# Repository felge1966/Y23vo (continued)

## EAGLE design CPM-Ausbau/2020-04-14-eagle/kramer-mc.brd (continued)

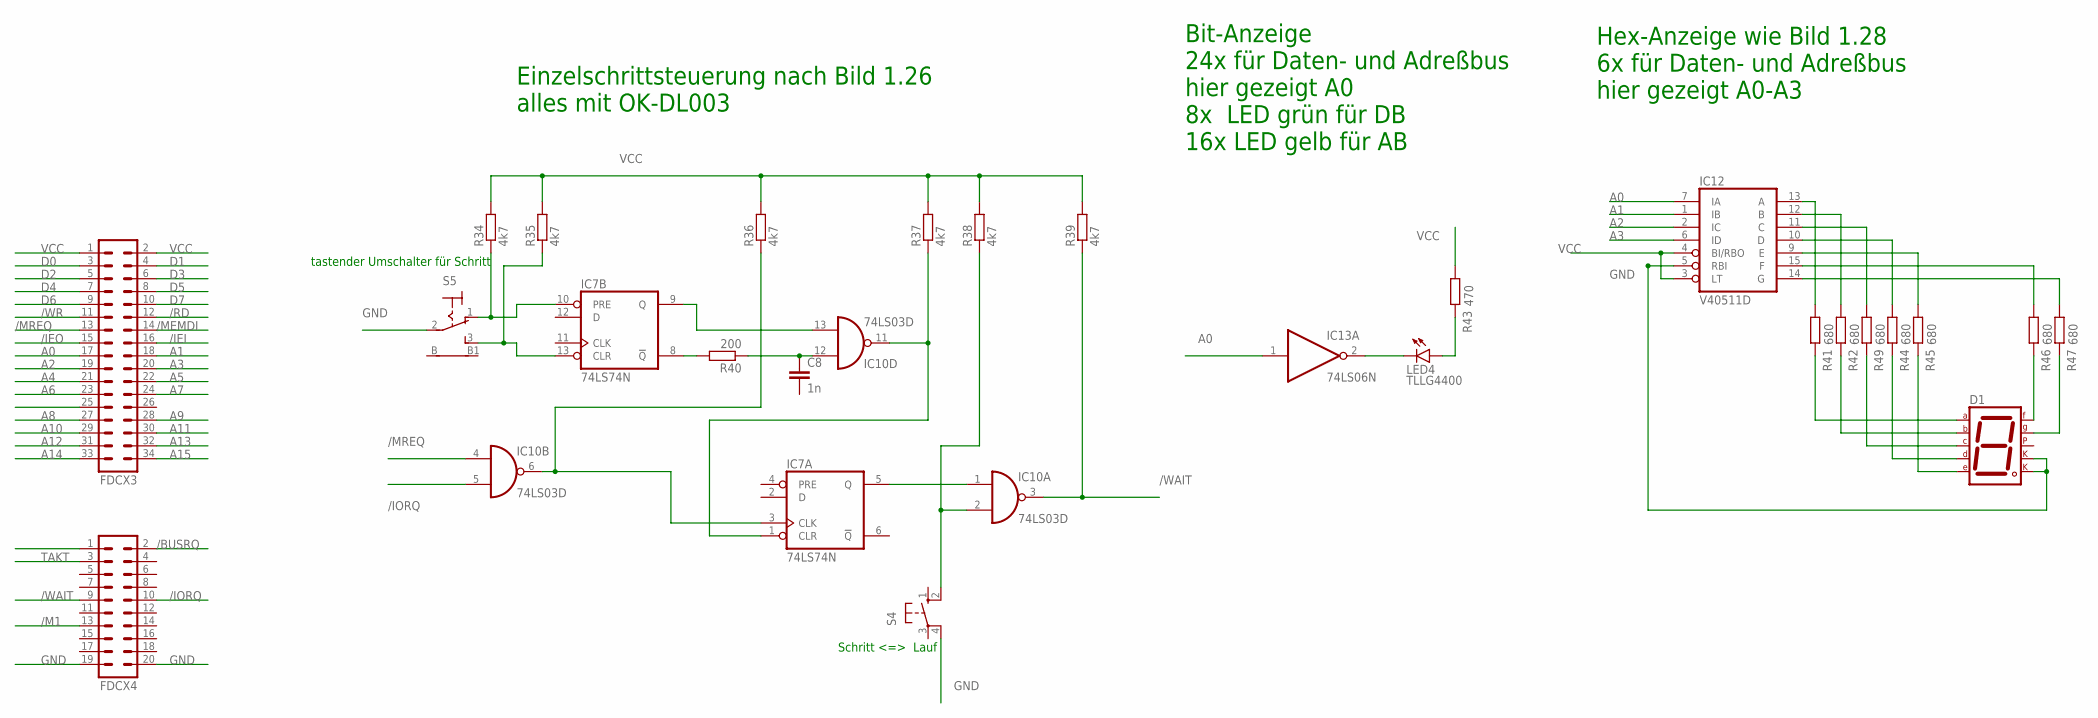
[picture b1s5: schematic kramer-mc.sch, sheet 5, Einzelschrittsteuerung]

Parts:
C8: 1n; C050-024X044
D1: 7SEG-CK; 7SEG-13
FDCX3: ML34
FDCX4: ML20
IC7: 74LS74N; DIL14
IC10: 74LS03D; SO14
IC12: V40511D; DIL16
IC13: 74LS06N; DIL14
LED4: TLLG4400; LED3MM
R34, R35, R36, R37, R38, R39: 4k7; 0309/12
R40: 200; 0309/12
R41, R42, R44, R45, R46, R47, R49: 680; 0309/12
R43: 470; 0309/12
S4: 10-XX; B3F-10XX
S5: 316-917

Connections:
/BUSRQ: FDCX4.2; also elsewhere on the board
/CSBWS1: FDCX3.25
/IEI: FDCX3.16; also elsewhere on the board
/IEO: FDCX3.15; also elsewhere on the board
/IORQ: FDCX4.10, IC10.5 (I1); also elsewhere on the board
/M1: FDCX4.13; also elsewhere on the board
/MEMDI: FDCX3.14; also elsewhere on the board
/MREQ: FDCX3.13, IC10.4 (I0); also elsewhere on the board
/RD: FDCX3.12; also elsewhere on the board
/RESET1: FDCX4.1
/WAIT: FDCX4.9, IC10.3 (O), R39.1; also elsewhere on the board
/WR: FDCX3.11; also elsewhere on the board
A0: FDCX3.17, IC12.7 (IA), IC13.1 (I); also elsewhere on the board
A1: FDCX3.18, IC12.1 (IB); also elsewhere on the board
A2: FDCX3.19, IC12.2 (IC); also elsewhere on the board
A3: FDCX3.20, IC12.6 (ID); also elsewhere on the board
A4: FDCX3.21; also elsewhere on the board
A5: FDCX3.22; also elsewhere on the board
A6: FDCX3.23; also elsewhere on the board
A7: FDCX3.24; also elsewhere on the board
A8: FDCX3.27; also elsewhere on the board
A9: FDCX3.28; also elsewhere on the board
A10: FDCX3.29; also elsewhere on the board
A11: FDCX3.30; also elsewhere on the board
A12: FDCX3.31; also elsewhere on the board
A13: FDCX3.32; also elsewhere on the board
A14: FDCX3.33; also elsewhere on the board
A15: FDCX3.34; also elsewhere on the board
D0: FDCX3.3; also elsewhere on the board
D1: FDCX3.4; also elsewhere on the board
D2: FDCX3.5; also elsewhere on the board
D3: FDCX3.6; also elsewhere on the board
D4: FDCX3.7; also elsewhere on the board
D5: FDCX3.8; also elsewhere on the board
D6: FDCX3.9; also elsewhere on the board
D7: FDCX3.10; also elsewhere on the board
GND: D1.3 (CK1), D1.8 (CK2), FDCX4.19, FDCX4.20, IC7.7 (GND), IC10.7 (GND), IC12.5 (RBI), IC12.8 (GND), IC13.7 (GND), S4.4 (P1), S5.2; also elsewhere on the board
unnamed: IC7.10 (PRE), R34.1, S5.1 (O)
unnamed: IC7.13 (CLR), R35.1, S5.3 (S)
unnamed: IC7.9 (Q), IC10.13 (I1)
unnamed: IC12.13 (A), R41.1
unnamed: IC7.8 (!Q), R40.2
unnamed: C8.1, IC10.12 (I0), R40.1
unnamed: IC7.1 (CLR), IC10.11 (O), R37.1
unnamed: IC10.2 (I1), R38.1, S4.2 (S1)
unnamed: IC7.5 (Q), IC10.1 (I0)
unnamed: IC12.12 (B), R42.1
unnamed: IC7.3 (CLK), IC10.6 (O), R36.1
unnamed: IC12.11 (C), R49.1
unnamed: IC12.10 (D), R44.1
unnamed: IC12.9 (E), R45.1
unnamed: IC13.2 (O), LED4.K (C)
unnamed: LED4.A, R43.2
unnamed: IC12.15 (F), R46.1
unnamed: IC12.14 (G), R47.1
unnamed: D1.7 (A), R41.2
unnamed: D1.6 (B), R42.2
unnamed: D1.10 (G), R47.2
unnamed: D1.9 (F), R46.2
unnamed: D1.4 (C), R49.2
unnamed: D1.2 (D), R44.2
unnamed: D1.1 (E), R45.2
TAKT: FDCX4.3; also elsewhere on the board
VCC: FDCX3.1, FDCX3.2, IC7.14 (VCC), IC10.14 (VCC), IC12.3 (LT), IC12.4 (BI/RBO), IC12.16 (VCC), IC13.14 (VCC), R34.2, R35.2, R36.2, R37.2, R38.2, R39.2, R43.1; also elsewhere on the board

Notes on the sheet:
tastender Umschalter für Schritt
Schritt <=> Lauf
Einzelschrittsteuerung nach Bild 1.26 alles mit OK-DL003
Hex-Anzeige wie Bild 1.28 6x für Daten- und Adreßbus hier gezeigt A0-A3
Bit-Anzeige 24x für Daten- und Adreßbus hier gezeigt A0 8x LED grün für DB 16x LED gelb für AB

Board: 2 copper layers, 159 parts (0 on the bottom side), 286 nets, no tracks yet.

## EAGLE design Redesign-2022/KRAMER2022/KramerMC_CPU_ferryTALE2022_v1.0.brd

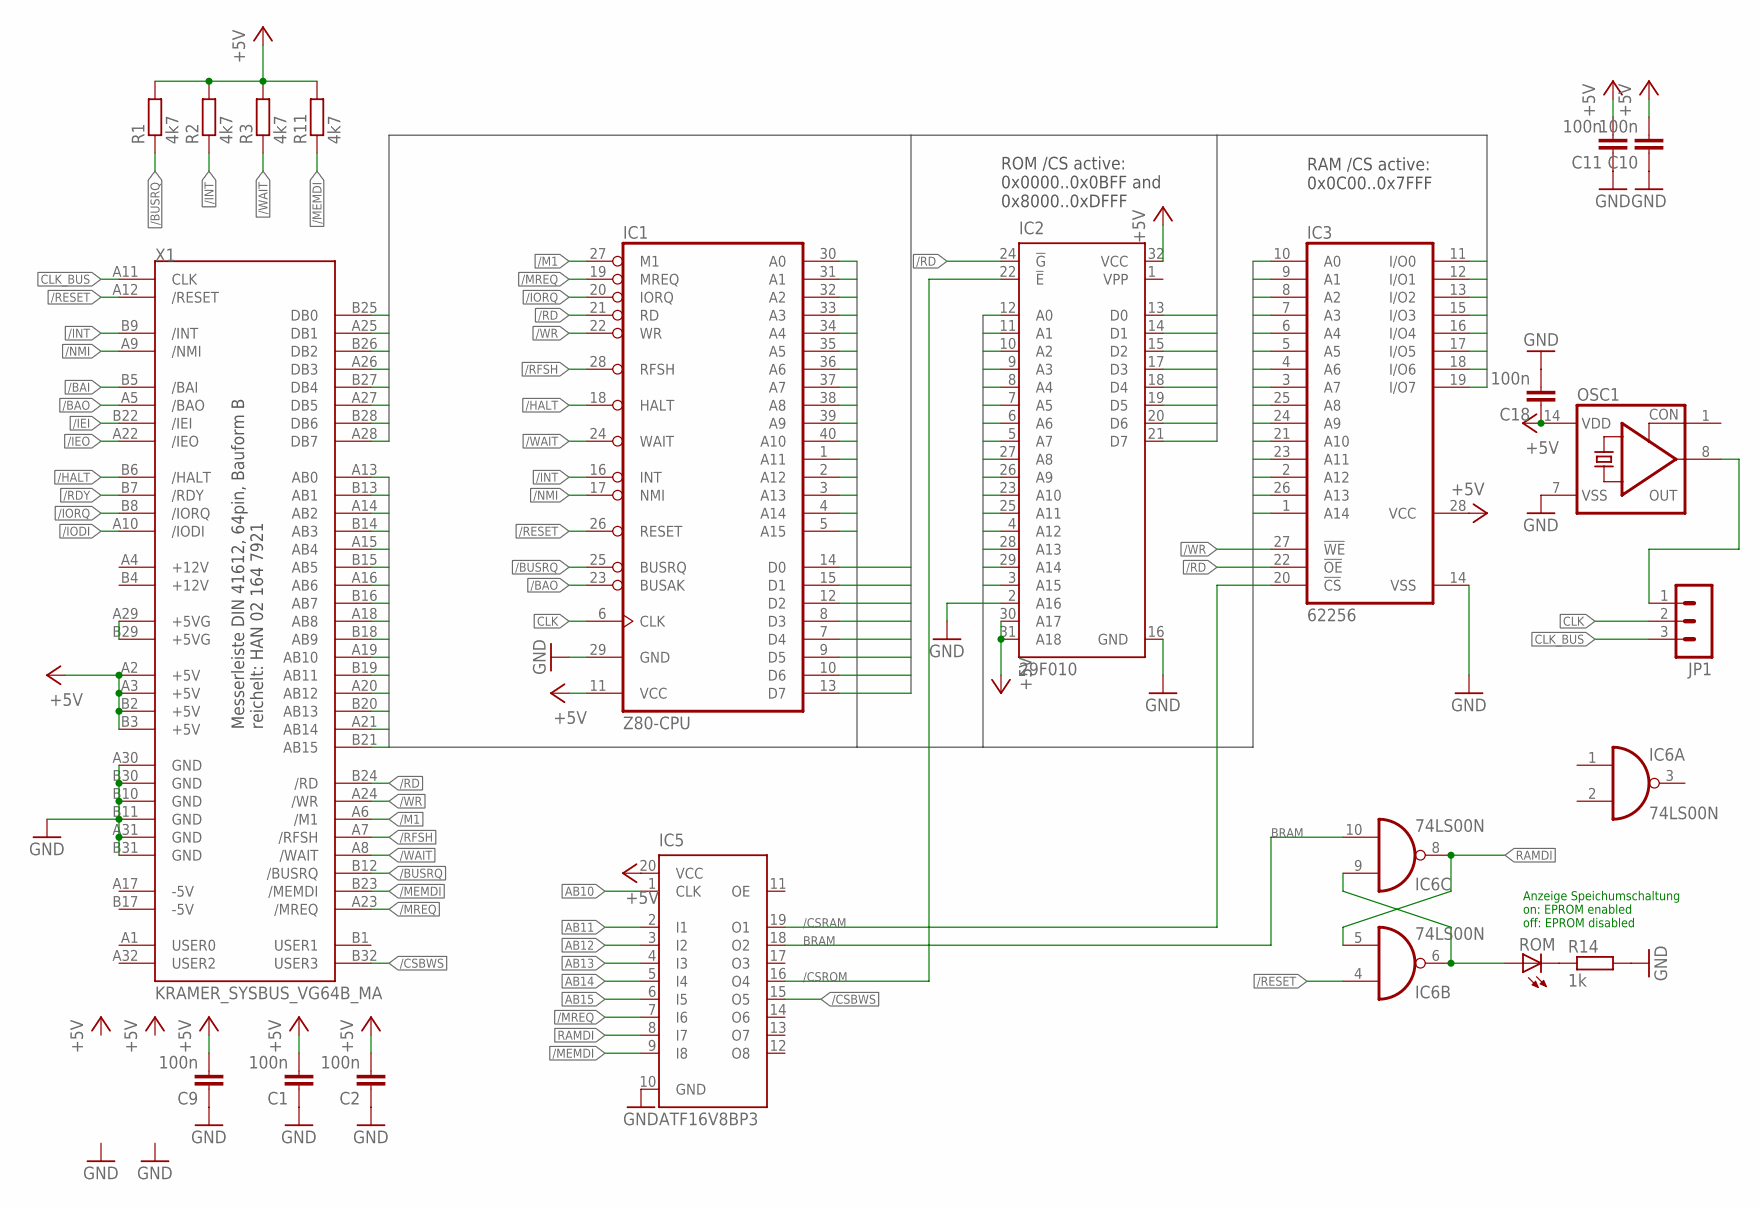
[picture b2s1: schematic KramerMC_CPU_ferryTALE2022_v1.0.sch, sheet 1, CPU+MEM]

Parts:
C1, C2, C9, C10, C11, C18: 100n; C050-024X044
IC1: Z80-CPU; DIL40
IC2: 29F010; DIL32
IC3: 62256; DIL28-6
IC5: ATF16V8BP3; DIL20
IC6: 74LS00N; DIL14
JP1: MA03-1
OSC1: CRYSTAL_RES-SG51; SG51
R1, R2, R3, R11: 4k7; 0207/10
R14: 1k; 0207/10
ROM: LED3MM
X1: KRAMER_SYSBUS_VG64B_MA; MAB64

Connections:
+5V: C1.2, C2.2, C9.2, C10.2, C11.2, C18.1, IC1.11 (VCC), IC2.30 (A17), IC2.31 (A18), IC2.32 (VCC), IC3.28 (VCC), IC5.20 (VCC), OSC1.14 (VDD), R1.2, R2.2, R3.2, R11.2, X1.A2 (+5V), X1.A3 (+5V), X1.B2 (+5V), X1.B3 (+5V); also elsewhere on the board
+5VG: X1.A29 (+5VG), X1.B29 (+5VG)
/BAI: X1.B5 (/BAI)
/BAO: IC1.23 (BUSAK), X1.A5 (/BAO)
/BUSRQ: IC1.25 (BUSRQ), R1.1, X1.B12 (/BUSRQ)
/CSBWS: IC5.15 (O5), X1.B32 (USER3)
/CSRAM: IC3.20 (!CS), IC5.19 (O1)
/CSROM: IC2.22 (!E), IC5.16 (O4)
/HALT: IC1.18 (HALT), X1.B6 (/HALT)
/IEI: X1.B22 (/IEI)
/IEO: X1.A22 (/IEO)
/INT: IC1.16 (INT), R2.1, X1.B9 (/INT); also elsewhere on the board
/IODI: X1.A10 (/IODI)
/IORQ: IC1.20 (IORQ), X1.B8 (/IORQ); also elsewhere on the board
/M1: IC1.27 (M1), X1.A6 (/M1); also elsewhere on the board
/MEMDI: IC5.9 (I8), R11.1, X1.B23 (/MEMDI)
/MREQ: IC1.19 (MREQ), IC5.7 (I6), X1.A23 (/MREQ)
/NMI: IC1.17 (NMI), X1.A9 (/NMI); also elsewhere on the board
/RD: IC1.21 (RD), IC2.24 (!G), IC3.22 (!OE), X1.B24 (/RD); also elsewhere on the board
/RDY: X1.B7 (/RDY)
/RESET: IC1.26 (RESET), IC6.4 (I0), X1.A12 (/RESET); also elsewhere on the board
/RFSH: IC1.28 (RFSH), X1.A7 (/RFSH)
/WAIT: IC1.24 (WAIT), R3.1, X1.A8 (/WAIT)
/WR: IC1.22 (WR), IC3.27 (!WE), X1.A24 (/WR)
AB0: IC1.30 (A0), IC2.12 (A0), IC3.10 (A0), X1.A13 (AB0); also elsewhere on the board
AB1: IC1.31 (A1), IC2.11 (A1), IC3.9 (A1), X1.B13 (AB1); also elsewhere on the board
AB2: IC1.32 (A2), IC2.10 (A2), IC3.8 (A2), X1.A14 (AB2)
AB3: IC1.33 (A3), IC2.9 (A3), IC3.7 (A3), X1.B14 (AB3)
AB4: IC1.34 (A4), IC2.8 (A4), IC3.6 (A4), X1.A15 (AB4)
AB5: IC1.35 (A5), IC2.7 (A5), IC3.5 (A5), X1.B15 (AB5)
AB6: IC1.36 (A6), IC2.6 (A6), IC3.4 (A6), X1.A16 (AB6); also elsewhere on the board
AB7: IC1.37 (A7), IC2.5 (A7), IC3.3 (A7), X1.B16 (AB7); also elsewhere on the board
AB8: IC1.38 (A8), IC2.27 (A8), IC3.25 (A8), X1.A18 (AB8)
AB9: IC1.39 (A9), IC2.26 (A9), IC3.24 (A9), X1.B18 (AB9)
AB10: IC1.40 (A10), IC2.23 (A10), IC3.21 (A10), IC5.1 (CLK), X1.A19 (AB10)
AB11: IC1.1 (A11), IC2.25 (A11), IC3.23 (A11), IC5.2 (I1), X1.B19 (AB11)
AB12: IC1.2 (A12), IC2.4 (A12), IC3.2 (A12), IC5.3 (I2), X1.A20 (AB12)
AB13: IC1.3 (A13), IC2.28 (A13), IC3.26 (A13), IC5.4 (I3), X1.B20 (AB13)
AB14: IC1.4 (A14), IC2.29 (A14), IC3.1 (A14), IC5.5 (I4), X1.A21 (AB14)
AB15: IC1.5 (A15), IC2.3 (A15), IC5.6 (I5), X1.B21 (AB15)
BRAM: IC5.18 (O2), IC6.10 (I1)
CLK: IC1.6 (CLK), JP1.2; also elsewhere on the board
CLK_BUS: JP1.3, X1.A11 (CLK)
DB0: IC1.14 (D0), IC2.13 (D0), IC3.11 (I/O0), X1.B25 (DB0); also elsewhere on the board
DB1: IC1.15 (D1), IC2.14 (D1), IC3.12 (I/O1), X1.A25 (DB1); also elsewhere on the board
DB2: IC1.12 (D2), IC2.15 (D2), IC3.13 (I/O2), X1.B26 (DB2); also elsewhere on the board
DB3: IC1.8 (D3), IC2.17 (D3), IC3.15 (I/O3), X1.A26 (DB3); also elsewhere on the board
DB4: IC1.7 (D4), IC2.18 (D4), IC3.16 (I/O4), X1.B27 (DB4); also elsewhere on the board
DB5: IC1.9 (D5), IC2.19 (D5), IC3.17 (I/O5), X1.A27 (DB5); also elsewhere on the board
DB6: IC1.10 (D6), IC2.20 (D6), IC3.18 (I/O6), X1.B28 (DB6); also elsewhere on the board
DB7: IC1.13 (D7), IC2.21 (D7), IC3.19 (I/O7), X1.A28 (DB7); also elsewhere on the board
GND: C1.1, C2.1, C9.1, C10.1, C11.1, C18.2, IC1.29 (GND), IC2.2 (A16), IC2.16 (GND), IC3.14 (VSS), IC5.10 (GND), OSC1.7 (VSS), R14.2, X1.A30 (GND), X1.A31 (GND), X1.B10 (GND), X1.B11 (GND), X1.B30 (GND), X1.B31 (GND); also elsewhere on the board
unnamed: IC6.6 (O), IC6.9 (I0), ROM.A
unnamed: R14.1, ROM.K (C)
unnamed: JP1.1, OSC1.8 (OUT)
RAMDI: IC5.8 (I7), IC6.5 (I1), IC6.8 (O)
VPP: IC2.1 (VPP)

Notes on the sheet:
RAM /CS active: 0x0C00..0x7FFF
ROM /CS active: 0x0000..0x0BFF and 0x8000..0xDFFF
Anzeige Speichumschaltung on: EPROM enabled off: EPROM disabled
Messerleiste DIN 41612, 64pin, Bauform B reichelt: HAN 02 164 7921

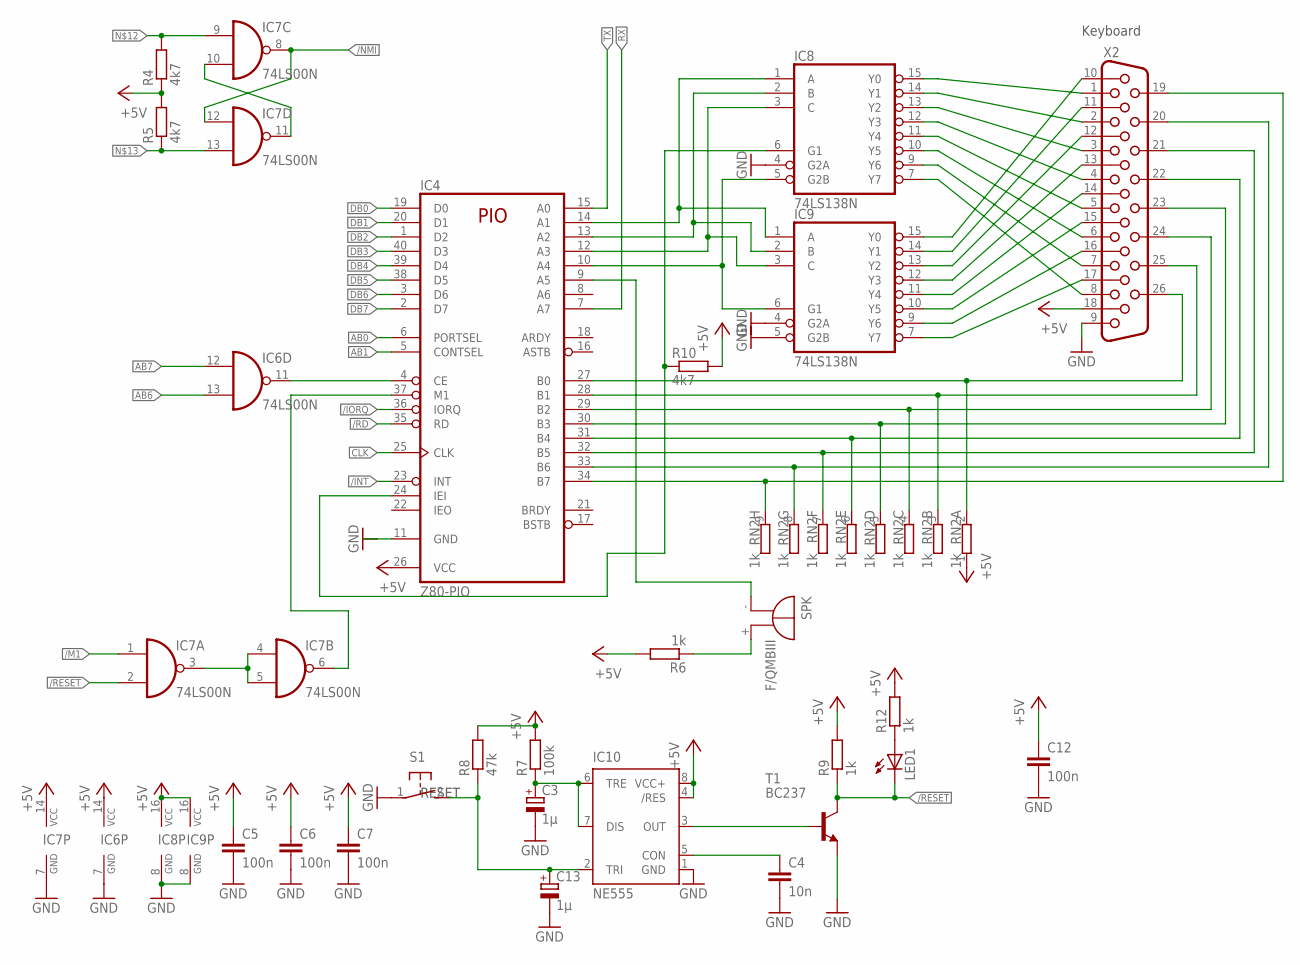
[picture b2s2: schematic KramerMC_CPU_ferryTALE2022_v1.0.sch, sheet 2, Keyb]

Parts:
C3, C13: 1µ; E2-5
C4: 10n; C050-024X044
C5, C6, C7, C12: 100n; C050-024X044
IC4: Z80-PIO; DIL40
IC6, IC7: 74LS00N; DIL14
IC8, IC9: 74LS138N; DIL16
IC10: NE555; DIL-08
LED1: LED3MM
R4, R5, R10: 4k7; 0207/10
R6: 1k; 0207/10
R7: 100k; 0207/2V
R8: 47k; 0207/10
R9, R12: 1k; 0207/2V
RN2: 1k; SIL9
S1: 31-XX; B3F-31XX
SPK: F/QMBIII
T1: BC237; TO92
X2: HF26H; HDF26H

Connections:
+5V: C5.1, C6.1, C7.1, C12.1, IC4.26 (VCC), IC6.14 (VCC), IC7.14 (VCC), IC8.16 (VCC), IC9.16 (VCC), IC10.4 (/RES), IC10.8 (VCC+), R4.1, R5.2, R6.2, R7.2, R8.2, R9.2, R10.2, R12.2, RN2.1, X2.18; also elsewhere on the board
/INT: IC4.23 (INT); also elsewhere on the board
/IORQ: IC4.36 (IORQ); also elsewhere on the board
/M1: IC7.1 (I0); also elsewhere on the board
/NMI: IC7.8 (O), IC7.12 (I0); also elsewhere on the board
/RD: IC4.35 (RD); also elsewhere on the board
/RESET: IC7.2 (I1), LED1.K (C), R9.1, T1.3 (C); also elsewhere on the board
AB0: IC4.6 (PORTSEL); also elsewhere on the board
AB1: IC4.5 (CONTSEL); also elsewhere on the board
AB6: IC6.13 (I1); also elsewhere on the board
AB7: IC6.12 (I0); also elsewhere on the board
CLK: IC4.25 (CLK); also elsewhere on the board
DB0: IC4.19 (D0); also elsewhere on the board
DB1: IC4.20 (D1); also elsewhere on the board
DB2: IC4.1 (D2); also elsewhere on the board
DB3: IC4.40 (D3); also elsewhere on the board
DB4: IC4.39 (D4); also elsewhere on the board
DB5: IC4.38 (D5); also elsewhere on the board
DB6: IC4.3 (D6); also elsewhere on the board
DB7: IC4.2 (D7); also elsewhere on the board
GND: C3.-, C4.2, C5.2, C6.2, C7.2, C12.2, C13.-, IC4.11 (GND), IC6.7 (GND), IC7.7 (GND), IC8.4 (G2A), IC8.8 (GND), IC9.4 (G2A), IC9.5 (G2B), IC9.8 (GND), IC10.1 (GND), S1.1, T1.1 (E), X2.9; also elsewhere on the board
unnamed: LED1.A, R12.1
unnamed: IC8.15 (Y0), X2.1
unnamed: IC7.10 (I1), IC7.11 (O)
unnamed: IC7.9 (I0), R4.2
unnamed: IC7.13 (I1), R5.1
unnamed: IC4.14 (A1), IC8.1 (A), IC9.1 (A)
unnamed: IC4.13 (A2), IC8.2 (B), IC9.2 (B)
unnamed: IC4.12 (A3), IC8.3 (C), IC9.3 (C)
unnamed: IC7.3 (O), IC7.4 (I0), IC7.5 (I1)
unnamed: IC8.14 (Y1), X2.2
unnamed: IC4.4 (CE), IC6.11 (O)
unnamed: IC4.37 (M1), IC7.6 (O)
unnamed: IC8.13 (Y2), X2.3
unnamed: IC8.12 (Y3), X2.4
unnamed: IC8.11 (Y4), X2.5
unnamed: IC8.10 (Y5), X2.6
unnamed: IC8.9 (Y6), X2.7
unnamed: IC8.7 (Y7), X2.8
unnamed: IC4.27 (B0), RN2.2, X2.26
unnamed: IC4.28 (B1), RN2.3 (2), X2.25
unnamed: IC4.29 (B2), RN2.4 (2), X2.24
unnamed: IC4.30 (B3), RN2.5 (2), X2.23
unnamed: IC4.31 (B4), RN2.6 (2), X2.22
unnamed: IC4.32 (B5), RN2.7 (2), X2.21
unnamed: IC4.33 (B6), RN2.8 (2), X2.20
unnamed: IC4.34 (B7), RN2.9 (2), X2.19
unnamed: IC4.9 (A5), SPK.- (+)
unnamed: IC10.3 (OUT), T1.2 (B)
unnamed: C3.+, IC10.6 (TRE), IC10.7 (DIS), R7.1
unnamed: C4.1, IC10.5 (CON)
unnamed: R6.1, SPK.+ (-)
unnamed: IC4.24 (IEI), IC8.6 (G1), R10.1
unnamed: IC4.10 (A4), IC8.5 (G2B), IC9.6 (G1)
unnamed: IC9.15 (Y0), X2.10
unnamed: IC9.14 (Y1), X2.11
unnamed: IC9.13 (Y2), X2.12
unnamed: IC9.12 (Y3), X2.13
unnamed: IC9.11 (Y4), X2.14
unnamed: IC9.10 (Y5), X2.15
unnamed: IC9.9 (Y6), X2.16
unnamed: IC9.7 (Y7), X2.17
RESET_BUTTON: C13.+, IC10.2 (TRI), R8.1, S1.2 (S)
RX: IC4.7 (A7); also elsewhere on the board
TX: IC4.15 (A0); also elsewhere on the board

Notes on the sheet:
Keyboard
RESET

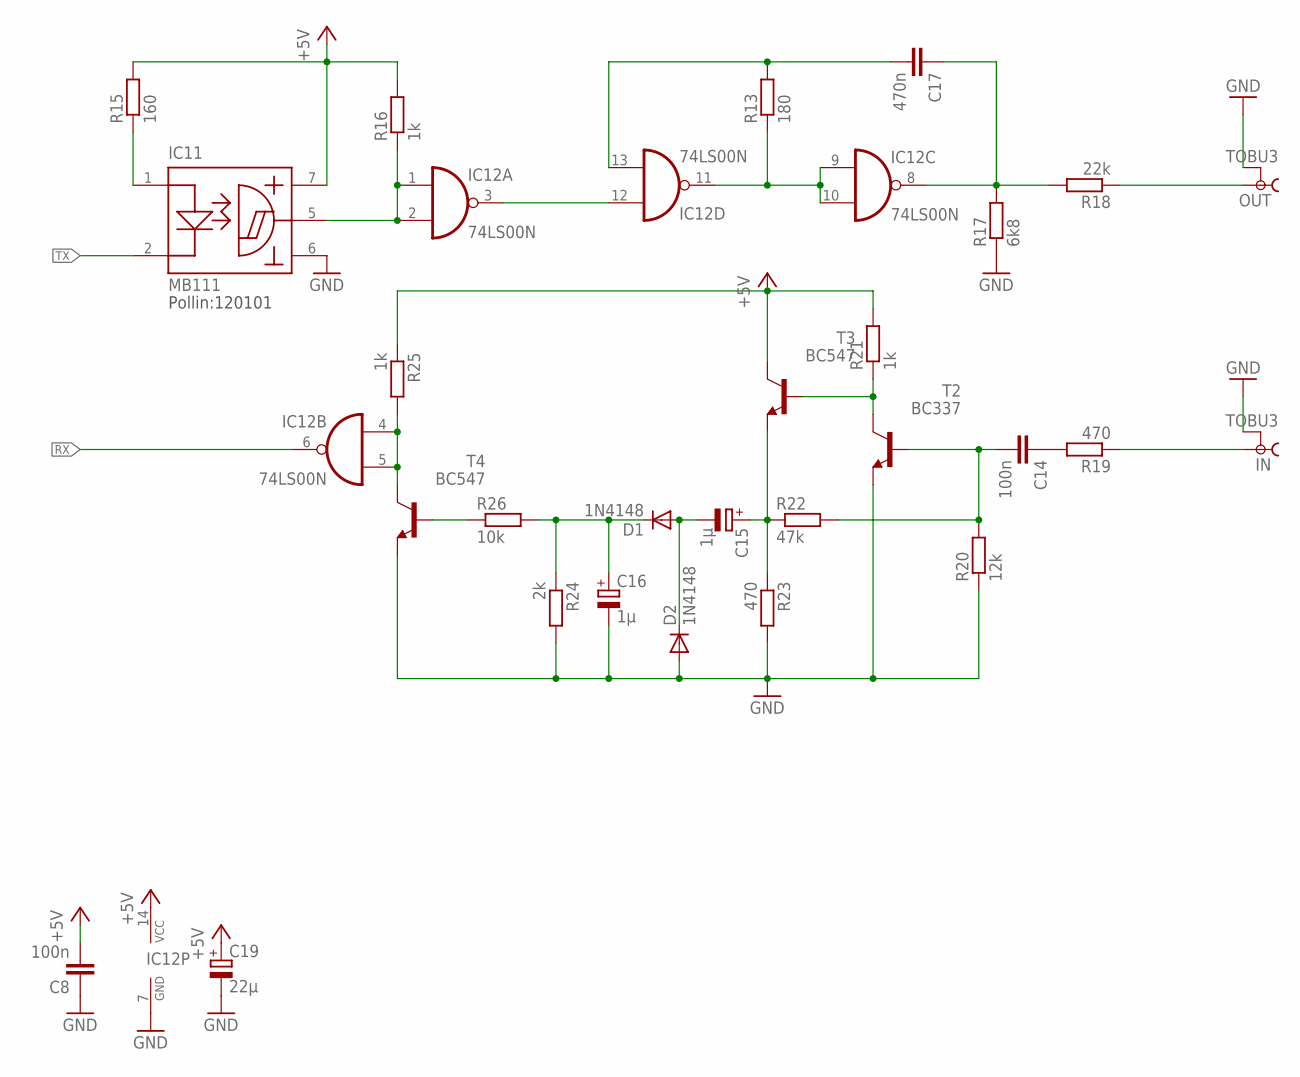
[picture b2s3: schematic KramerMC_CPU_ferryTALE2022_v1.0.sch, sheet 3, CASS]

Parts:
C8, C14: 100n; C050-024X044
C15, C16: 1µ; E2-4
C17: 470n; C050-024X044
C19: 22µ; E2-4
D1, D2: 1N4148; DO35-7
IC11: MB111; DIL08
IC12: 74LS00N; DIL14
IN: TOBU3
OUT: TOBU3
R13: 180; 0207/10
R15: 160; 0207/10
R16, R25: 1k; 0207/2V
R17: 6k8; 0207/10
R18: 22k; 0207/10
R19, R23: 470; 0207/10
R20: 12k; 0207/10
R21: 1k; 0207/10
R22: 47k; 0207/2V
R24: 2k; 0207/10
R26: 10k; 0207/10
T2: BC337; TO92
T3, T4: BC547; TO92

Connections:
+5V: C8.2, C19.+, IC11.7 (VCC), IC12.14 (VCC), R15.2, R16.2, R21.2, R25.1, T3.3 (C); also elsewhere on the board
GND: C8.1, C16.-, C19.-, D2.A, IC11.6 (GND), IC12.7 (GND), IN.2, IN.2@1 (2), IN.2@2 (2), OUT.2, OUT.2@1 (2), OUT.2@2 (2), R17.1, R20.1, R23.2, R24.2, T2.1 (E), T4.1 (E); also elsewhere on the board
unnamed: IC11.1 (A), R15.1
unnamed: IC12.3 (O), IC12.12 (I0)
unnamed: IC11.5 (OUT), IC12.1 (I0), IC12.2 (I1), R16.1
unnamed: C17.2, IC12.13 (I1), R13.2
unnamed: IC12.9 (I0), IC12.10 (I1), IC12.11 (O), R13.1
unnamed: OUT.1, R18.1
unnamed: IC12.4 (I0), IC12.5 (I1), R25.2, T4.3 (C)
unnamed: C14.1, R19.2
unnamed: C17.1, IC12.8 (O), R17.2, R18.2
unnamed: R21.1, T2.3 (C), T3.2 (B)
unnamed: C14.2, R20.2, R22.2, T2.2 (B)
unnamed: IN.1, R19.1
unnamed: R26.1, T4.2 (B)
unnamed: C16.+, D1.C, R24.1, R26.2
unnamed: C15.-, D1.A, D2.C
unnamed: C15.+, R22.1, R23.1, T3.1 (E)
RX: IC12.6 (O); also elsewhere on the board
TX: IC11.2 (K); also elsewhere on the board

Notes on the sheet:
Pollin:120101

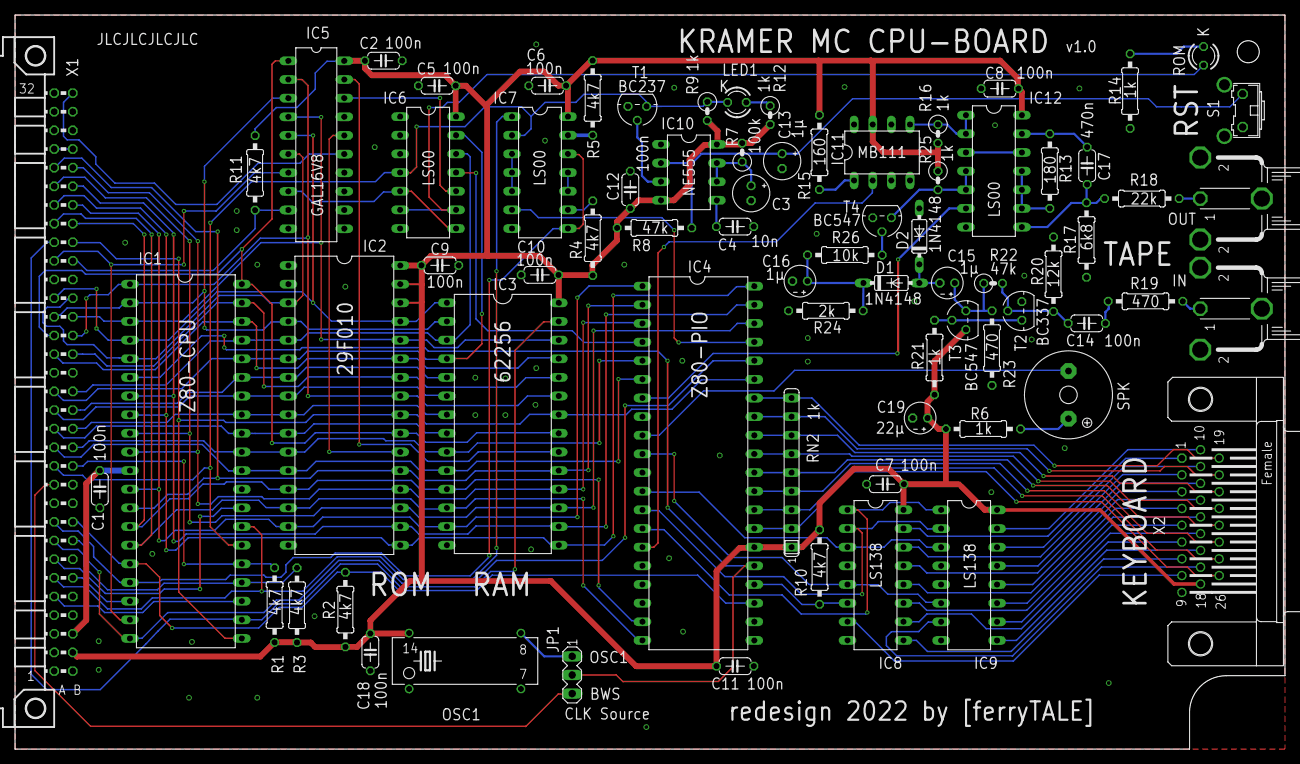
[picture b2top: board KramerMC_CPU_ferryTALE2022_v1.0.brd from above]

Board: 2 copper layers, 173.0 x 100.0 mm, 74 parts (0 on the bottom side), 111 nets.

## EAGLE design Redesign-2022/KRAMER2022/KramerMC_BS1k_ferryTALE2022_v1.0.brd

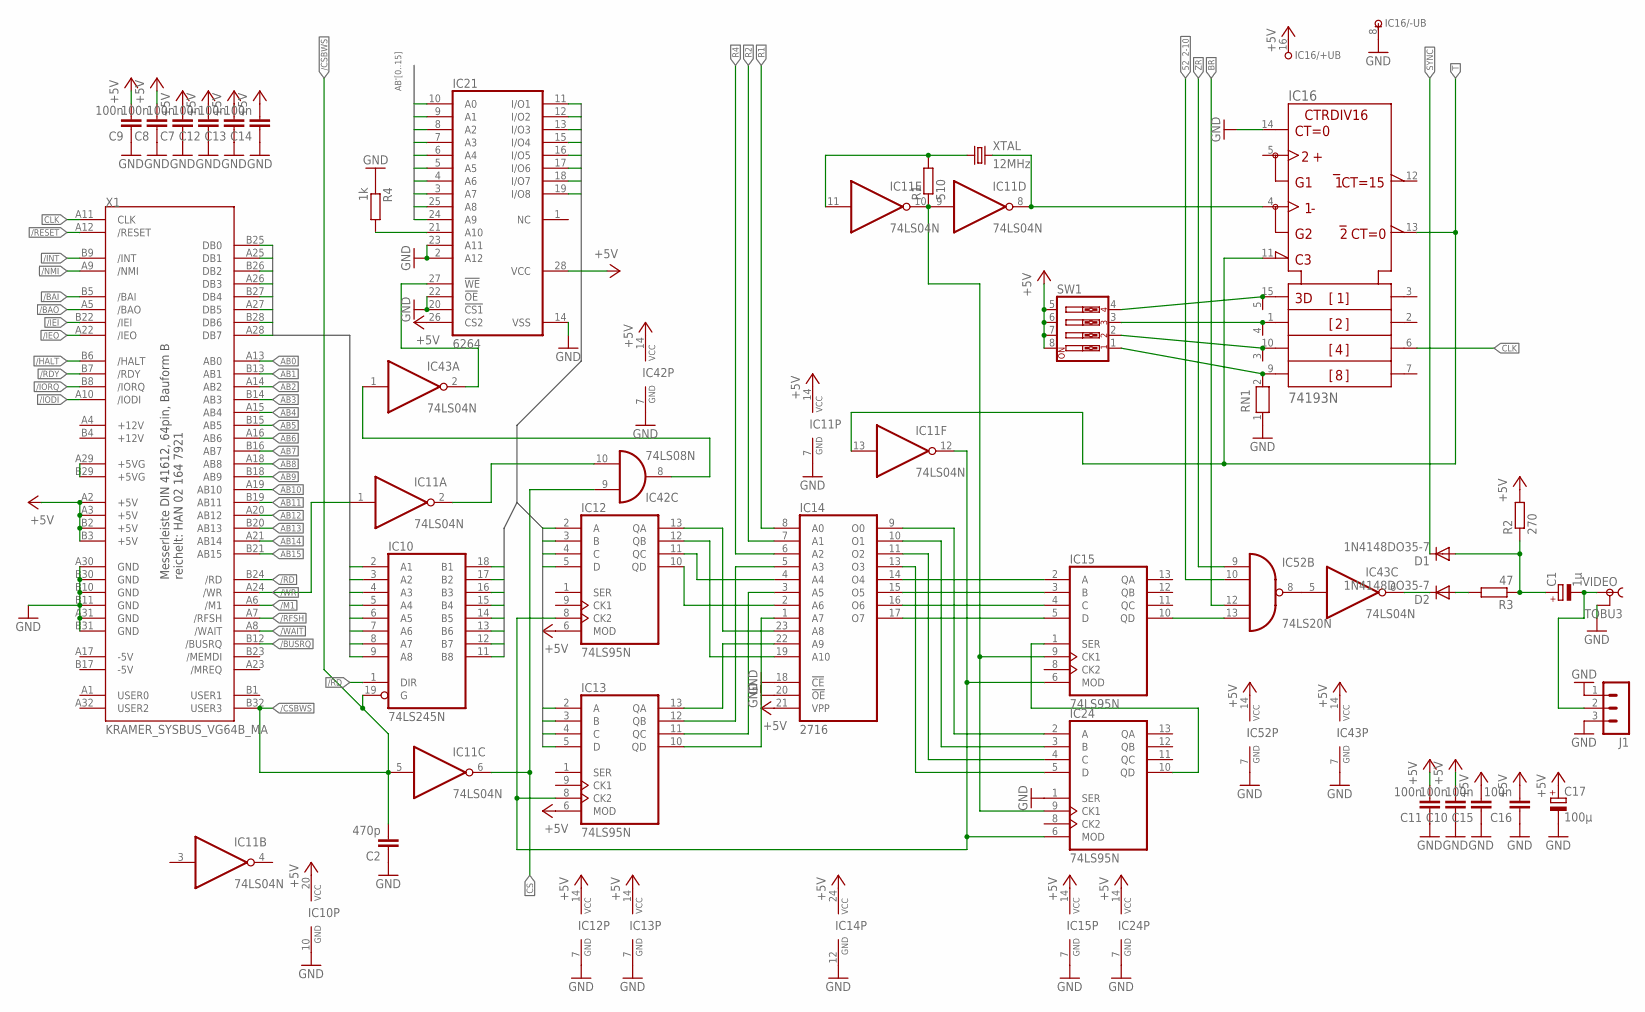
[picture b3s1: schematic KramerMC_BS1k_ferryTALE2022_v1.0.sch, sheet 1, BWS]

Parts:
C1: 1µ; E2,5-5
C2: 470p; C050-024X044
C7, C8, C9, C10, C11, C12, C13, C14, C15, C16: 100n; C050-024X044
C17: 100µ; E2,5-7
D1, D2: 1N4148DO35-7; DO35-7
IC10: 74LS245N; DIL20
IC11, IC43: 74LS04N; DIL14
IC12, IC13, IC15, IC24: 74LS95N; DIL14
IC14: 2716; DIL24
IC16: 74193N; DIL16
IC21: 6264; DIL28-6
IC42: 74LS08N; DIL14
IC52: 74LS20N; DIL14
J1: MA03-1
R1: 510; 0207/2V
R2: 270; 0207/10
R3: 47; 0207/10
R4: 1k; 0207/10
RN1: RN04; RN-5
SW1: SW_DIP-4; EDG-04
VIDEO: TOBU3
X1: KRAMER_SYSBUS_VG64B_MA; MAB64
XTAL: 12MHz; HC49/S

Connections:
52_2-10: IC52.10 (I1); also elsewhere on the board
+5V: C7.2, C8.2, C9.2, C10.2, C11.2, C12.2, C13.2, C14.2, C15.2, C16.2, C17.+, IC10.20 (VCC), IC11.14 (VCC), IC12.6 (MOD), IC12.14 (VCC), IC13.6 (MOD), IC13.14 (VCC), IC14.21 (VPP), IC14.24 (VCC), IC15.14 (VCC), IC16.16 (+UB), IC21.26 (CS2), IC21.28 (VCC), IC24.14 (VCC), IC42.14 (VCC), IC43.14 (VCC), IC52.14 (VCC), R2.2, SW1.5, SW1.6, SW1.7, SW1.8, X1.A2 (+5V), X1.A3 (+5V), X1.B2 (+5V), X1.B3 (+5V); also elsewhere on the board
+5VG: X1.A29 (+5VG), X1.B29 (+5VG)
/BAI: X1.B5 (/BAI)
/BAO: X1.A5 (/BAO)
/BUSRQ: X1.B12 (/BUSRQ)
/CSBWS: C2.2, IC10.19 (G), IC11.5 (I), X1.B32 (USER3); also elsewhere on the board
/HALT: X1.B6 (/HALT)
/IEI: X1.B22 (/IEI)
/IEO: X1.A22 (/IEO)
/INT: X1.B9 (/INT)
/IODI: X1.A10 (/IODI)
/IORQ: X1.B8 (/IORQ)
/M1: X1.A6 (/M1)
/NMI: X1.A9 (/NMI)
/RD: IC10.1 (DIR), X1.B24 (/RD)
/RDY: X1.B7 (/RDY)
/RESET: X1.A12 (/RESET)
/RFSH: X1.A7 (/RFSH)
/WAIT: X1.A8 (/WAIT)
/WR: IC11.1 (I), X1.A24 (/WR)
AB0: X1.A13 (AB0); also elsewhere on the board
AB1: X1.B13 (AB1); also elsewhere on the board
AB2: X1.A14 (AB2); also elsewhere on the board
AB3: X1.B14 (AB3); also elsewhere on the board
AB4: X1.A15 (AB4); also elsewhere on the board
AB5: X1.B15 (AB5); also elsewhere on the board
AB6: X1.A16 (AB6); also elsewhere on the board
AB7: X1.B16 (AB7); also elsewhere on the board
AB8: X1.A18 (AB8); also elsewhere on the board
AB9: X1.B18 (AB9); also elsewhere on the board
AB10: X1.A19 (AB10)
AB11: X1.B19 (AB11)
AB12: X1.A20 (AB12)
AB13: X1.B20 (AB13)
AB14: X1.A21 (AB14)
AB15: X1.B21 (AB15)
AB'0: IC21.10 (A0); also elsewhere on the board
AB'1: IC21.9 (A1); also elsewhere on the board
AB'2: IC21.8 (A2); also elsewhere on the board
AB'3: IC21.7 (A3); also elsewhere on the board
AB'4: IC21.6 (A4); also elsewhere on the board
AB'5: IC21.5 (A5); also elsewhere on the board
AB'6: IC21.4 (A6); also elsewhere on the board
AB'7: IC21.3 (A7); also elsewhere on the board
AB'8: IC21.25 (A8); also elsewhere on the board
AB'9: IC21.24 (A9); also elsewhere on the board
BR: IC52.12 (I2); also elsewhere on the board
CLK: IC16.6 (QC), X1.A11 (CLK)
CS: IC11.6 (O), IC42.9 (I0); also elsewhere on the board
DB0: IC10.9 (A8), X1.B25 (DB0)
DB1: IC10.8 (A7), X1.A25 (DB1)
DB2: IC10.7 (A6), X1.B26 (DB2)
DB3: IC10.6 (A5), X1.A26 (DB3)
DB4: IC10.5 (A4), X1.B27 (DB4)
DB5: IC10.4 (A3), X1.A27 (DB5)
DB6: IC10.3 (A2), X1.B28 (DB6)
DB7: IC10.2 (A1), X1.A28 (DB7)
DB'0: IC10.11 (B8), IC13.3 (B), IC21.11 (I/O1)
DB'1: IC10.12 (B7), IC12.4 (C), IC21.12 (I/O2)
DB'2: IC10.13 (B6), IC13.4 (C), IC21.13 (I/O3)
DB'3: IC10.14 (B5), IC12.5 (D), IC21.15 (I/O4)
DB'4: IC10.15 (B4), IC13.5 (D), IC21.16 (I/O5)
DB'5: IC10.16 (B3), IC12.2 (A), IC21.17 (I/O6)
DB'6: IC10.17 (B2), IC13.2 (A), IC21.18 (I/O7)
DB'7: IC10.18 (B1), IC12.3 (B), IC21.19 (I/O8)
GND: C2.1, C7.1, C8.1, C9.1, C10.1, C11.1, C12.1, C13.1, C14.1, C15.1, C16.1, C17.-, IC10.10 (GND), IC11.7 (GND), IC12.7 (GND), IC13.7 (GND), IC14.12 (GND), IC14.18 (!CE), IC14.20 (!OE), IC15.7 (GND), IC16.8 (-UB), IC16.14 (CLR), IC21.2 (A12), IC21.14 (VSS), IC21.20 (!CS1), IC21.22 (!OE), IC21.23 (A11), IC24.1 (SER), IC24.7 (GND), IC42.7 (GND), IC43.7 (GND), IC52.7 (GND), J1.1, J1.3, R4.1, RN1.1, VIDEO.2, VIDEO.2@1 (2), VIDEO.2@2 (2), X1.A30 (GND), X1.A31 (GND), X1.B10 (GND), X1.B11 (GND), X1.B30 (GND), X1.B31 (GND); also elsewhere on the board
unnamed: IC11.9 (I), IC11.10 (O), IC15.9 (CK1), IC24.9 (CK1), R1.1
unnamed: IC11.11 (I), R1.2, XTAL.1
unnamed: IC11.8 (O), IC16.4 (DOWN), XTAL.2
unnamed: IC12.13 (QA), IC14.23 (A8)
unnamed: IC12.12 (QB), IC14.19 (A10)
unnamed: IC12.11 (QC), IC14.4 (A4)
unnamed: IC12.10 (QD), IC14.2 (A6)
unnamed: IC13.13 (QA), IC14.22 (A9)
unnamed: IC13.12 (QB), IC14.5 (A3)
unnamed: IC13.11 (QC), IC14.3 (A5)
unnamed: IC13.10 (QD), IC14.1 (A7)
unnamed: IC14.17 (O7), IC15.5 (D)
unnamed: IC11.2 (O), IC42.10 (I1)
unnamed: IC42.8 (O), IC43.1 (I)
unnamed: IC21.27 (!WE), IC43.2 (O)
unnamed: IC14.16 (O6), IC15.4 (C)
unnamed: IC14.15 (O5), IC15.3 (B)
unnamed: C1.-, J1.2, VIDEO.1
unnamed: IC14.14 (O4), IC15.2 (A)
unnamed: IC43.5 (I), IC52.8 (O)
unnamed: IC14.13 (O3), IC24.5 (D)
unnamed: IC14.11 (O2), IC24.4 (C)
unnamed: IC14.10 (O1), IC24.3 (B)
unnamed: IC14.9 (O0), IC24.2 (A)
unnamed: IC15.1 (SER), IC24.10 (QD)
unnamed: IC11.12 (O), IC12.8 (CK2), IC13.8 (CK2), IC15.6 (MOD), IC24.6 (MOD)
unnamed: C1.+, D1.A, R2.1, R3.1
unnamed: IC15.10 (QD), IC52.13 (I3)
unnamed: IC16.15 (A), RN1.5, SW1.4
unnamed: D2.A, R3.2
unnamed: D2.C, IC43.6 (O)
unnamed: IC16.1 (B), RN1.4, SW1.3
unnamed: IC16.10 (C), RN1.3, SW1.2
unnamed: IC16.9 (D), RN1.2, SW1.1
unnamed: IC21.21 (A10), R4.2
R1: IC14.8 (A0); also elsewhere on the board
R2: IC14.7 (A1); also elsewhere on the board
R4: IC14.6 (A2); also elsewhere on the board
SYNC: D1.C; also elsewhere on the board
T: IC11.13 (I), IC16.11 (!LOAD), IC16.13 (!BO); also elsewhere on the board
ZR: IC52.9 (I0); also elsewhere on the board

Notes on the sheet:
Messerleiste DIN 41612, 64pin, Bauform B reichelt: HAN 02 164 7921
